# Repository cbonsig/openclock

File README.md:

openclock
=========

A clock designed to resolve the flaws of every annoying alarm clock that I've ever owned. Large display that can be easily read with uncorrected vision, adaptive brightness based on the time of day, intuitive touchscreen interface, clear feedback on the state of the alarm, intelligent alarm audio. Powered by Arduino. A work in progress. Journal of effort to date at http://clock.bonsignore.com

Open Clock Project by Craig Bonsignore is licensed under a Creative Commons Attribution-ShareAlike 3.0 United States License.Based on a work at http://clock.bonsignore.com.

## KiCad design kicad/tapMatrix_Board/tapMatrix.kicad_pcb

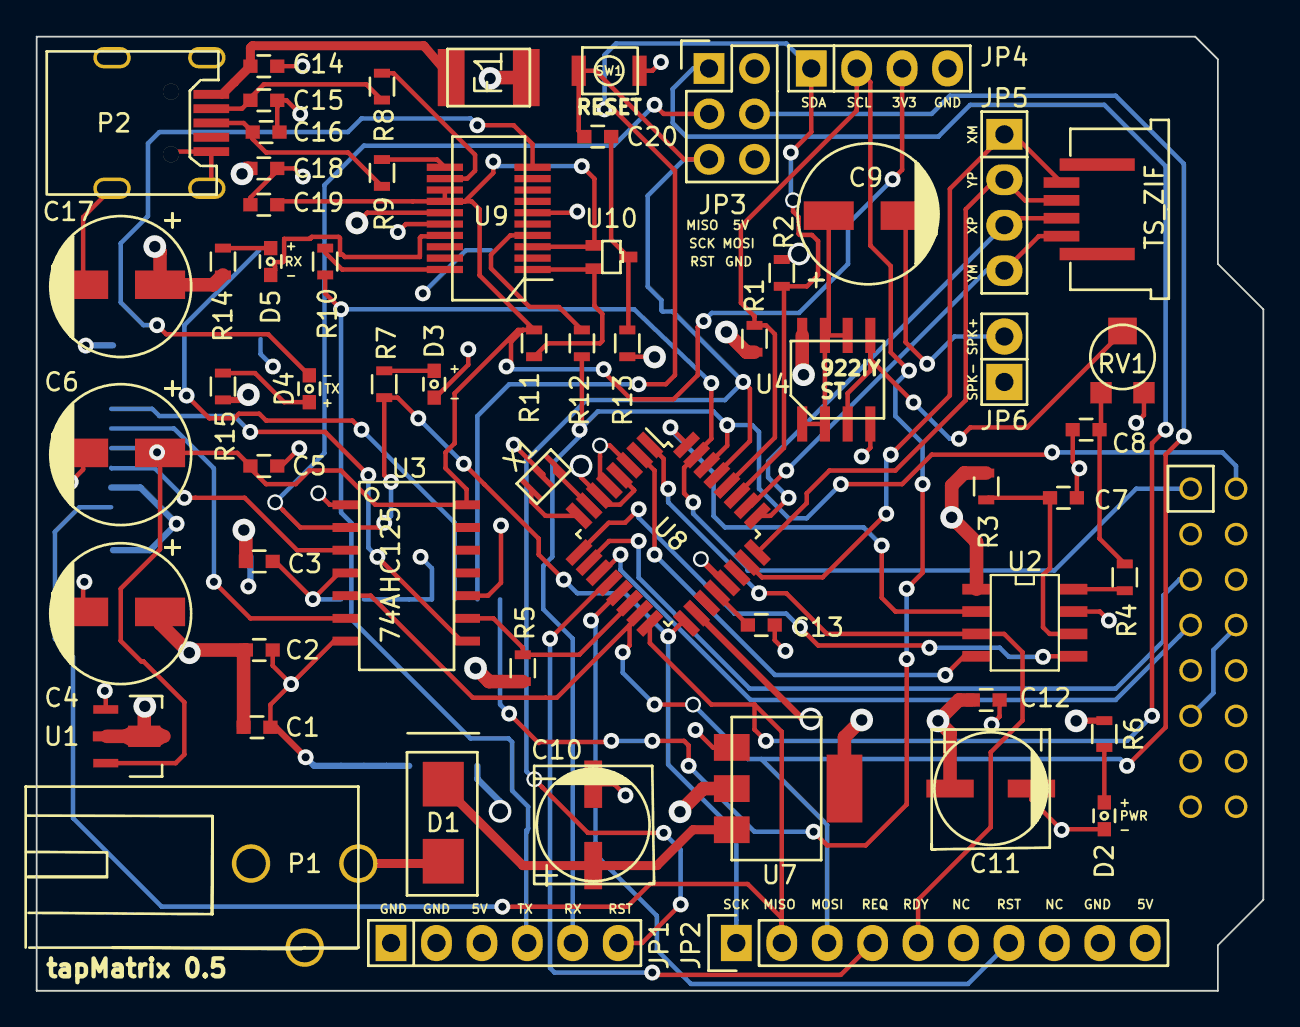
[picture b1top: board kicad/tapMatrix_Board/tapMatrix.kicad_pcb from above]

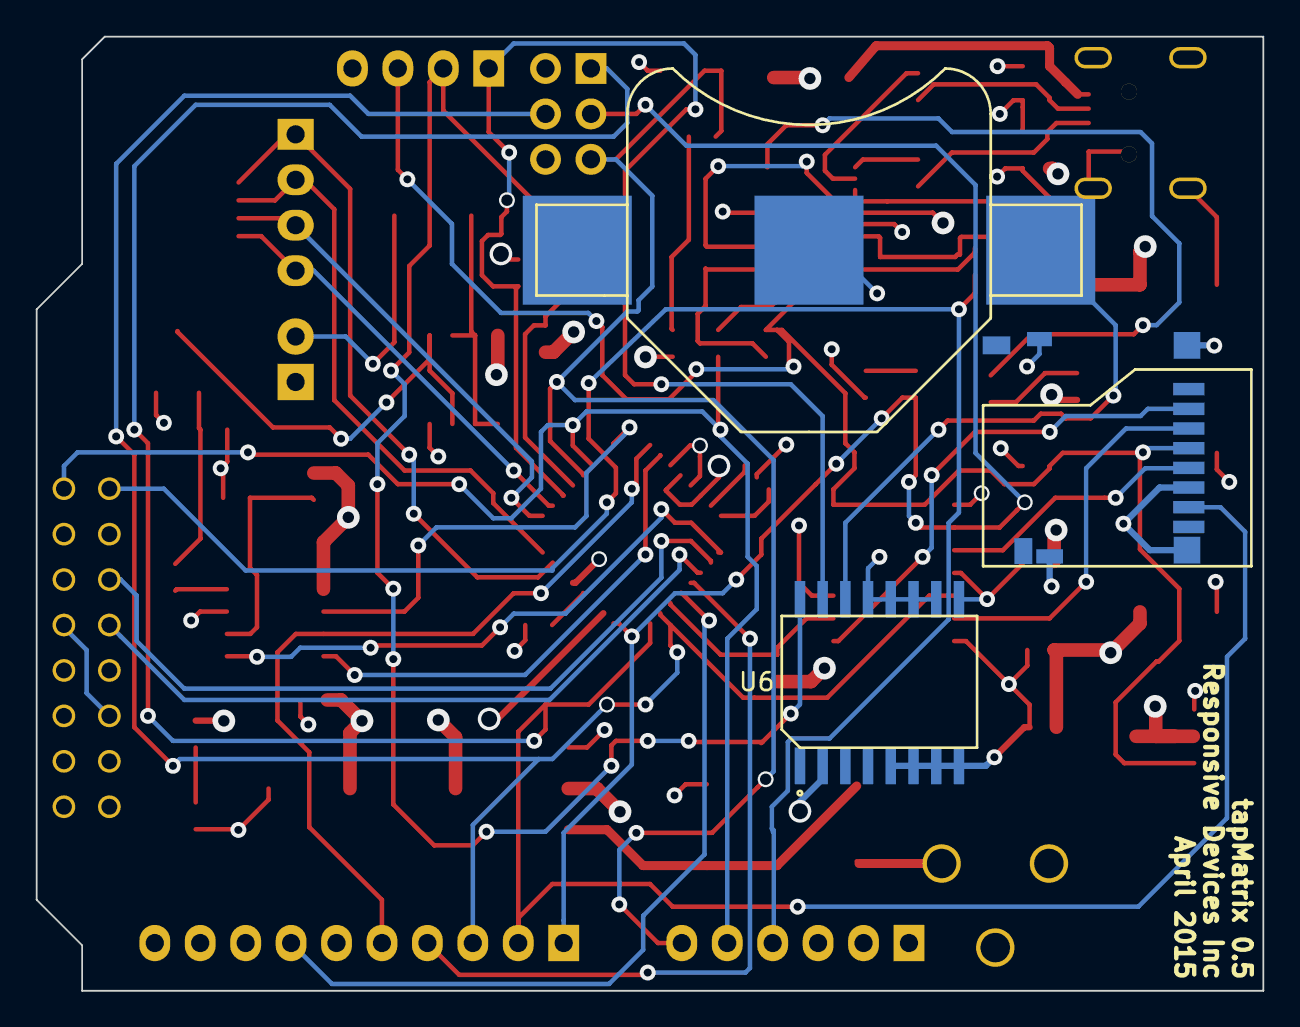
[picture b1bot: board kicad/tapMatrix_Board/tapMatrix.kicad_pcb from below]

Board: 4 copper layers, 68.6 x 53.3 mm, 65 parts (3 on the bottom side), 54 nets.

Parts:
BT1: BATTERY; CR2032
C1, C2, C3, C5, C7, C12, C13, C14, C18, C19, C20: 0.1uF; C_0603
C4, C6, C9: 100uF/6V; EEE-0JA101WR
C8: 0.01uF; C_0603
C10, C11: 47uF; CAP_MVA_F55
C15, C16: 47pF; C_0603
C17: 4.7uF; EEE-0JA101WR
D1: DIODE; DS16004
D2, D3: LED; D_0603
D4: TXLED; D_0603
D5: RXLED; D_0603
F1: 500mA; Fuse_MF_MSMF
JP1: FTDI; Pin_Header_Straight_1x06
JP2: nRF8001; Pin_Header_Straight_1x10
JP3: ICSP; Pin_Header_Straight_2x03
JP4: 4_PIN_2; Pin_Header_Straight_1x04
JP5: 4_PIN_1; Pin_Header_Straight_1x04
JP6: SPKR; Pin_Header_Straight_1x02
P1: +9V Power; PJ-102AH
P2: USB-MINI-B; USBMiniB_UX60_MB_5S8
P5: TS_ZIF; SFW4R­5STE1LF
P6: LED_MATRIX_HDR; 5103310­-3
R1, R2: R; R_0603
R3: 100K; R_0603
R4: 1.5K; R_0603
R5, R11, R13: 10K; R_0603
R6, R7: 510; R_0603
R8, R9: 27; R_0603
R10, R12, R14, R15: 1K; R_0603
RESET: SW_PUSH; SW_3BU_1000P
RV1: POT; TC33X
U1: MCP1703; SOT89-3_Housing
U2: MCP4921-E/SN; SOIC-8_N
U3: 74AHC125; SO-14
U4: TS922; TS922_SO8
U5: SD_CARD; 114-00841-68
U6: DS3231
U7: NCP1117ST50T3G; SOT223_318H
U8: ATMEGA328P-A; TQFP-32_7x7mm_Pitch0.8mm
U9: FT231XS; SSOP20_FTDI231X
U10: 2N7002PW; SOT-323
X1: CRYSTAL_SMD; XTAL_CSTCE_V

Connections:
+5V: C1.1, C2.1, C3.1, C4.1, C11.1, C12.1, C17.1, C18.1, F1.2, JP1.3, JP2.10, JP3.2, P6.12, P6.14, P6.16, R1.1, R2.1, R3.1, R5.1, R6.1, R13.1, R14.2, R15.2, U1.2, U2.1, U4.8, U6.2, U7.2, U8.4, U8.6, U8.18, U9.15
/CS: U3.8, U5.2
/D8: JP2.4, U8.12
/D9: JP2.7, U8.13
/DAC_CS: U2.2, U8.32
/DAC_DI: U2.4, U8.2
/DAC_LAT: U2.5, U8.9
/DAC_SCK: JP2.5, U2.3, U8.1
/DATA_IN: U3.6, U5.3
/I2C_SCL: JP4.2, R1.2, U6.16, U8.28
/I2C_SDA: JP4.1, R2.2, U6.15, U8.27
/MATRIX_CLK: JP1.5, P6.2, R12.2, U8.30
/MATRIX_CS: JP1.4, P6.1, R10.2, U8.31
/MATRIX_DATA: P6.7, U8.11
/MATRIX_WR: P6.5, U8.10
/MISO: JP2.2, JP3.1, U5.7, U8.16
/MOSI: JP2.3, JP3.4, U3.5, U8.15
/RESET: C20.1, JP1.6, JP3.5, RESET.2, U8.29
/SCK: JP2.1, JP3.3, R7.2, U3.2, U8.17
/SCLK: U3.3, U5.5
/SD_CS: R5.2, U3.9, U8.14
/XM: JP5.1, P5.1, U8.23
/XP: JP5.3, P5.3, U8.25
/YM: JP5.4, P5.4, U8.26
/YP: JP5.2, P5.2, U8.24
GND: BT1.2, C1.2, C2.2, C3.2, C4.2, C5.2, C6.2, C7.1, C8.2, C10.2, C11.2, C12.2, C13.2, C14.2, C15.2, C16.2, C17.2, C18.2, C19.2, D2.2, D3.2, JP1.1, JP1.2, JP2.9, JP3.6, JP4.4, JP6.1, P1.2, P1.3, P2.5, P2.6, P2.7, P2.8, P2.9, P6.8, P6.11, P6.13, P6.15, RESET.1, RV1.3, U1.1, U2.7, U3.1, U3.4, U3.7, U3.10, U4.4, U5.6, U5.G1, U5.G2, U5.G3, U5.G4, U6.5, U6.6, U6.7, U6.8, U6.9, U6.10, U6.11, U6.12, U6.13, U7.1, U8.3, U8.5, U8.21, U9.6, U9.16, X1.2
unnamed: BT1.1, U6.14
unnamed: C7.2, R3.2, U2.6
unnamed: C8.1, R4.1, RV1.1
unnamed: C9.1, U4.1, U4.2, U4.6, U4.7
unnamed: C9.2, JP6.2
unnamed: C10.1, D1.2, U7.3
unnamed: C13.1, U8.20
unnamed: C14.1, F1.1, P2.1
unnamed: C15.1, P2.2, R8.1
unnamed: C16.1, P2.3, R9.1
unnamed: C20.2, R13.2, U10.3
unnamed: D1.1, P1.1
unnamed: D2.1, R6.2
unnamed: D3.1, R7.1
unnamed: D4.1, R15.1
unnamed: D4.2, U9.10
unnamed: D5.1, R14.1
unnamed: D5.2, U9.17
unnamed: R4.2, U2.8
unnamed: R8.2, U9.12
unnamed: R9.2, U9.11
unnamed: R10.1, U9.20
unnamed: R11.2, U9.1, U10.2
unnamed: R12.1, U9.4
unnamed: RV1.2, U4.3, U4.5
unnamed: U8.7, X1.1
unnamed: U8.8, X1.3
VCC: C5.1, C6.1, C19.1, JP4.3, R11.1, U1.3, U3.14, U5.4, U9.3, U9.13, U9.14, U10.1

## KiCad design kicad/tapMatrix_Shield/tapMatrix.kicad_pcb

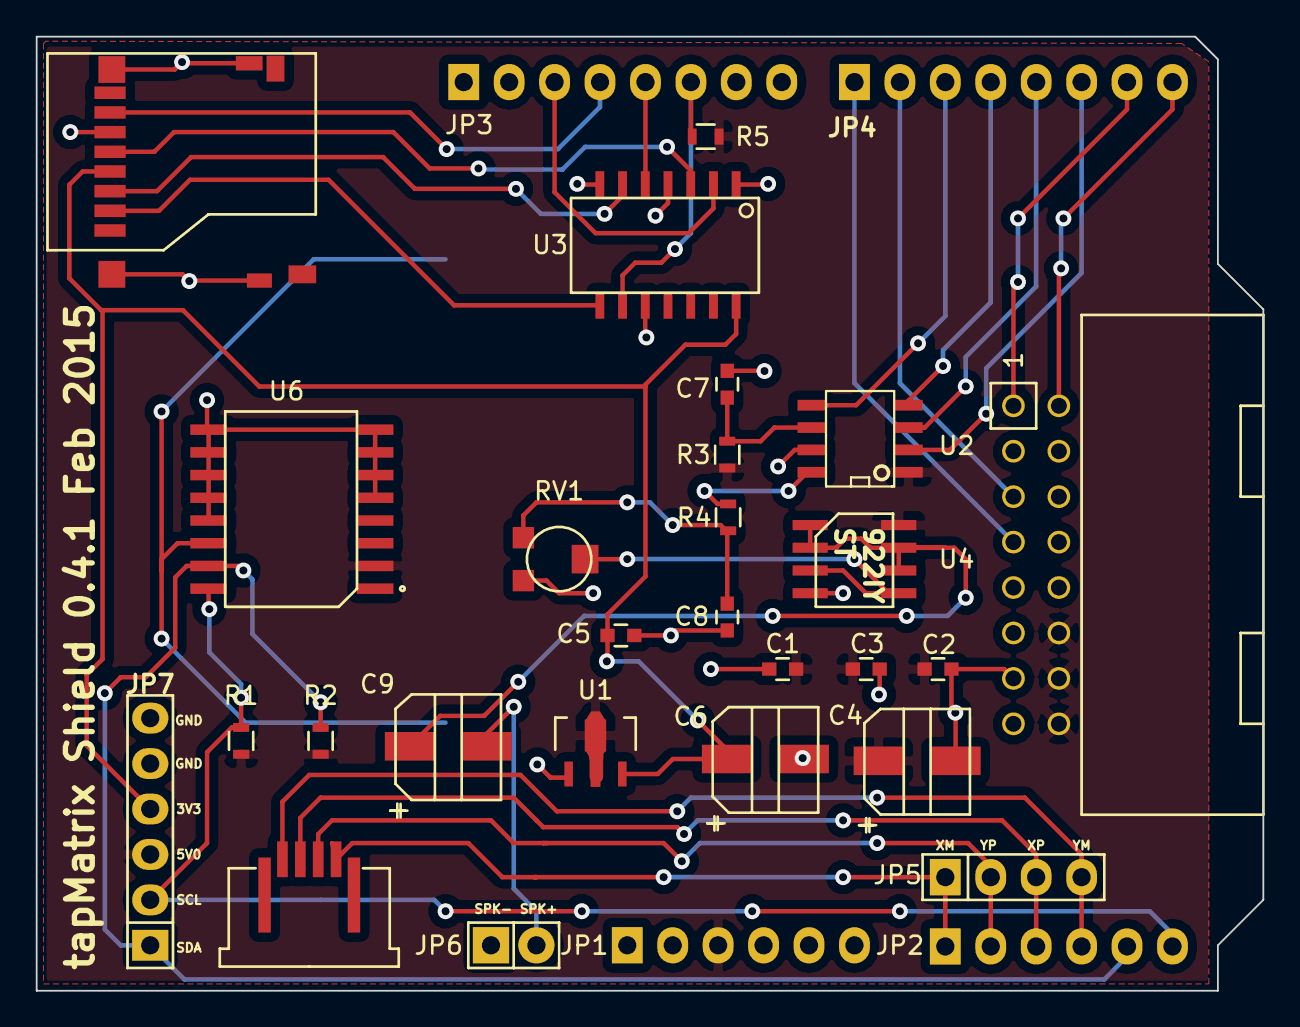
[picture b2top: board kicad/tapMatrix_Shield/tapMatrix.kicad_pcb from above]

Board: 2 copper layers, 68.6 x 53.3 mm, 31 parts (1 on the bottom side), 31 nets.

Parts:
BT1: CR2032
C1, C2, C3, C5, C7: 0.1uF; C_0603
C4, C6, C9: 100uF/6V; EEE-0JA101WR
C8: 0.01uF; C_0603
JP1: 6_PIN_1; Pin_Header_Straight_1x06
JP2: 6_PIN_2; Pin_Header_Straight_1x06
JP3: 8_PIN_1; Pin_Header_Straight_1x08
JP4: 8_PIN_2; Pin_Header_Straight_1x08
JP5: 4_PIN_1; Pin_Header_Straight_1x04
JP6: SPKR; Pin_Header_Straight_1x02
JP7: 6_PIN_3; Pin_Header_Straight_1x06
P5: TS_ZIF; SFW4R­5STE1LF
P6: LED_MATRIX_HDR; 5103310­-3
R1, R2: R; R_0603
R3: 100K; R_0603
R4: 1.5K; R_0603
R5: 10K; R_0603
RV1: POT; TC33X
U1: MCP1703; SOT89-3_Housing
U2: MCP4921-E/SN; SOIC-8_N
U3: 74LS125; SO-14
U4: TS922; TS922_SO8
U5: SD_CARD; 114-00841-68
U6: DS3231

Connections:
+3.3V: C5.1, C6.1, JP7.4, U1.3, U3.14, U5.4
+5V: C1.1, C2.1, C3.1, C4.1, JP1.3, JP7.3, P6.12, P6.14, P6.16, R1.1, R2.1, R3.1, R5.1, U1.2, U2.1, U4.8, U6.2
/CS: U3.8, U5.2
/DAC_CS: JP4.6, U2.2
/DAC_DI: JP4.4, U2.4
/DAC_LAT: JP4.3, U2.5
/DAC_SCK: JP4.5, U2.3
/DATA_IN: U3.6, U5.3
/I2C_SCL: JP2.6, JP7.2, R1.2, U6.16
/I2C_SDA: JP2.5, JP7.1, R2.2, U6.15
/MATRIX_CLK: JP4.8, P6.2
/MATRIX_CS: JP4.7, P6.1
/MATRIX_DATA: JP4.1, P6.7
/MATRIX_WR: JP4.2, P6.5
/MISO: JP3.4, U5.7
/MOSI: JP3.5, U3.5
/SCK: JP3.3, U3.2
/SCLK: U3.3, U5.5
/SD_CS: JP3.6, R5.2, U3.9
/XM: JP2.1, JP5.1, P5.1
/XP: JP2.3, JP5.3, P5.3
/YM: JP2.4, JP5.4, P5.4
/YP: JP2.2, JP5.2, P5.2
GND: BT1.2, C1.2, C2.2, C3.2, C4.2, C5.2, C6.2, C7.1, C8.2, JP1.4, JP1.5, JP3.2, JP6.1, JP7.5, JP7.6, P6.8, P6.11, P6.13, P6.15, RV1.3, U1.1, U2.7, U3.1, U3.4, U3.7, U3.10, U4.4, U5.6, U5.G1, U5.G2, U5.G3, U5.G4, U6.5, U6.6, U6.7, U6.8, U6.9, U6.10, U6.11, U6.12, U6.13
unnamed: BT1.1, U6.14
unnamed: C7.2, R3.2, U2.6
unnamed: C8.1, R4.1, RV1.1
unnamed: C9.1, U4.1, U4.2, U4.6, U4.7
unnamed: C9.2, JP6.2
unnamed: R4.2, U2.8
unnamed: RV1.2, U4.3, U4.5

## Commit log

2012-08-22 Initial commit for sketches and related libraries
2012-08-22 Add Solidworks parts and assembly
2012-08-26 Update README.md
    Add description of project.
2012-08-26 Update README.md
    Add reference to CC Attribution-ShareAlike 3.0 license
2012-11-17 rename to openclock.ino
    renamed the file and directory for the main sketch. this and future
    revisions will be managed by githib.
2012-11-25 rewrite to make code more organized
    move contributed libraries to sketch folder, per Arduino 1.0.2
    guidance. major refactoring . created currentTime subroutine . all
    characters now defined by global variables . all characters drawn to
    screen in one place @ end of main loop(). preparation for adding a
    functional UI to set time and alarm . added draft flow diagram for UI
2012-12-03 refactoring and touch development
    more reorganization of the code, and development of the touch routines.
    currently message area displays x,y,z when touch pressure exceeds
    threshold. to do: assign a timer to touch events, map touch events to
    menu selections and +/- digits.
2012-12-03 Update openclock/openclock.ino
    Added a link to an explanation about why using a pin higher than 8 does not work.
2012-12-03 Fixed hour bug
2012-12-04 Virtual button development
    Touch activated virtual buttons [hr+], [hr-], [min+], [min-], [ampm],
    [msg] can be detected, and will be used later for menu, alarm, and
    set-time functions. For now, the button state is displayed in the
    message area.
2012-12-04 ix bug: midnight renders as 0:00
2012-12-04 Revert "ix bug: midnight renders as 0:00"
    This reverts commit d720b7c31345ddba16c0d397b14fbf2bdf63aabc.
2012-12-04 Revert "Revert "ix bug: midnight renders as 0:00""
    This reverts commit 11733e3db17b308eef8b654cf0011cb639cfc867.
2012-12-10 Beginning code for alarm mode
    Added barely functional code for entering alarm set mode, and setting
    the alarm time.
2012-12-17 Replace <Chronodot.h> with Arduino Time Library
    Swapped out Chronodot library for the Arduino Time Library to be more
    standardized. Auto-formatted to fix indent levels.
2013-02-05 reworked touch and menu functions
    improved functionality of alarm setting mode. Not quite prefected.
    Menu timer isn't resetting for some reason.
2013-02-10 temporary sketch feb09
    (throretically) improved timers by moving initiation to setup as
    intended... now, first entry into menu mode works perfectly… but,
    second entry into menu mode never returns to clock mode. can't upload
    this to clock, so i'm stashing it here for now, as sketch_feb09a
2013-02-27 UI design refinements
    Mock-ups of menu modes, and draft additions to flow chart
2013-03-03 major rewrite for menu/tap timers
2013-03-04 Debug + Rearrange menus
    Halfway implemented new menu scheme. TBD: revise display rendering for
    display states.
2013-03-05 Rough code for menu scheme completed
    Rough code for menu scheme completed. TBD: code RTC commits for alarm
    and time; fix handling of time set.
2013-03-06 debug . display logic refinement
2013-03-08 color change for alarm display; display formatting
2013-03-08 fix alarm color display, fix incrementation for am/pm
2013-03-08 add RTC commit for time
    added RTC commit for time (with a couple of days to go before DST
    begins!!)
2013-03-09 Fix date setting screens, add alarm on/off toggle
2013-03-09 minor edits. changed most int to byte
2013-03-10 Revert byte to int for tapZone and displayState to fix time set bug
2013-03-12 Fix set year display bug (20-1)
    Revert newYear from byte to int
2013-03-12 fix alarm color rendering on main screen
2013-03-12 Commenting improvements
2013-03-16 Reduce SRAM footprint by 32 bytes (not enough)
2013-03-16 Add Waveshield and cleanup
2013-03-16 Cleanup and waveshield
2013-03-17 Waveshield victory!
    Added Waveshield setup{} code, and confirmed audio functionality.
    CLK_TOWR.WAV is played when EXIT is selected from menu.
2013-03-17 prep for alarm. change alarmState from boolean to byte
    prep for alarm. change alarmState from boolean to byte. add #define
    lines for alarm states including active and snooze
2013-03-17 checkAlarm() added, basic alarm function working!
2013-03-17 reference interrupt thread
2013-03-31 Correct year display
    Fix display of year for case where year = 2000 (default year for new
    chronodot)
2013-03-31 Add clock sounds .WAV files
2013-04-10 Created folders for 3D enclosure and 2D enclosure designs
    Moved OpenClockSolidworks to enclosure_design/3D_rev1 and created
    enclosure_design/2D_rev1 with Inkscape, LibreCAD, and SolidWorks files
2013-04-20 Update Rev1 2D enclosure
    Revised SVG for 2D Rev 1 ("Box") enclosure based on small modifications
    required on first laser cut prototype.
2013-04-22 Enclosure Rev1A updates
2013-05-03 2d rev 2 curved enclosure, solidworks in progress
2013-05-04 Curved 2D Enclosure - Solidworks
    complete solidworks geometry for rev2 enclosure
2013-05-04 nothing to see here
2013-05-05 Updates to Solidworks enclosure design
2013-05-05 Enclosure Design
    Curved enclosure design in Solidworks + Inkscape
2013-05-05 Inkscape 2D design for enclosure
2013-10-08 Overdue update to SVG design. The _1315 version is the one that was actually cut.
2014-03-02 update gitignore
2014-03-02 admin
2014-08-17 Initial commit for KiCad project and empty schematic
2014-08-18 Added Arduino headers to schematic
2014-08-18 Added ZIF socket, created component library, fixed Arduino headers
2014-08-19 add led matrix header, microsd component, update libraries
2014-08-20 improved headers, replaced global labels with local labels
2014-08-21 confirm and revise quad-buffer and microsd schematic details
2014-08-22 add 3.3V power supply, DAC, AMP, and Speaker Out
2014-08-23 add real time clock to schematic
2014-08-24 schematic edits to resolve error checking messages
2014-08-25 added footprints for battery and ribbon sockets
2014-08-25 created power and signal netclasses, updated design rules for oshpark
2014-08-26 add microsd module
2014-08-27 begin routing pcb
2014-08-27 continue routing
2014-08-29 complete first attempt at routing
2014-08-29 removed volume pot; created gerber files
2014-08-29 Add .gitignore
2014-08-29 reference local ht1632c library
2014-09-02 replaced 100uF caps with avail footprint; moved vias; revised to 0.2;
2014-09-04 added optional 4-pin header as alt for touchscreen zif
2014-09-04 trying to get rid of .DS_store pollution
2014-09-04 more DS_store erradiction
2014-09-04 replace voltage regulator with corrected component
2014-09-04 update gerbers for revision to voltage regulator component
2014-09-04 add top and bottom solder paste layers to gerbers
2014-09-23 create v0.3_ fix problems with U1, U3, U4 components U1 used the wrong footprint. changed from SOT-23 to SOT-89-3 U3 used the narrow version of SOIC-14 (incorrectly named in library as SOIC-14_W). ch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
2014-10-24 Add data sheets for new 0.3 components
2014-10-27 Revised r0.3 components, tore up pcb
2014-10-28 move capacitor footprints to tapmatrix library
2014-10-28 move resistor footprints to tapmatrix library
2014-10-28 catch up with commits for moving R and C to tapmatrix library
2014-10-28 move pin header footprints to tapmatrix library
2014-10-28 move SOT-89-3 footprint to tapmatrix library
2014-10-28 moved SOIC footprints to tapmatrix library
2014-10-31 confirmed and revised IC footprints
2014-11-01 route v3 pcb, first draft
2014-11-01 resolved DRC errors in v0.3 layout
2014-11-01 clean up labels
2014-11-02 corrected duplicated .zip.zip extension
2014-11-02 revised layout to improve GND and +5V plane connectivity
2014-11-02 added paste files to gerbers for stencil. updated dwg revision date.
2014-11-03 revised C3 to link to tapMatrix library, other minor edits
    re-routed C3
    repositioned reference labels for caps
    changed U1 line width to be consistent with other components
2014-11-03 Revise data sheet filenames to be more descriptive
2014-11-03 add datasheet for micro-SD connector
2014-11-03 PNG of uSD
2014-11-03 corrected uSD connector footprint
2014-11-03 add overlay of uSD datasheet and footprint
2014-11-24 corrected error with U1 pins (2 and 3 were reversed)
2014-11-24 corrected JP4, where MATRIX_WR and MATRIX_DATA were reveresed
2014-11-24 Add data sheet for DAC
2014-12-15 Revised Arduino code for shield v0.3
    Reordered touchscreen wires A0-A3
2014-12-16 Add comment regarding RTC fix
2014-12-24 Add data sheets for DS3231 trimpot and TS922 opamp
2014-12-24 Updated schematic annotations
2014-12-24 Schematic: replaced RTC and added pot replaced DS1207 with DS3231 real time clock added potentiometer to amplifier circuit
2014-12-25 add footprints and headers, tear up layout
2014-12-25 revise schematic
2015-01-05 save project
2015-02-04 Correct reversed pins 2+3 on LDO
    Input and output pins were reversed on the MCP1703 voltage regulator.
    Corrected schematic, footprint, and layout.
2015-02-04 draft 4-layer version of board
2015-02-14 0.4.1 revision - new level shifter component, etc
    Replace quad buffer / level shifter with 74AHC125N components tolerant
    of VCC=3.3V. Correct mixed pins on LDO. Add labels for breakout pins,
    and refine silkscreen text.
2015-02-19 Start rev 0.5 board
2015-02-20 complete first draft of 0.5 board
    add headers for FTDI, I2C, other extra pins.
2015-02-21 Add ICSP header and power LED
2015-03-17 Add FTDI USB-UART
    Added schematics for FTDI, based on Sparkfun Redboard and FTDI
    reference schematics. Created symbols for FT231XS and 2N7002PW.
2015-03-17 Revised schematic for FTDI
2015-03-31 Add SPI header for nRF8001
2015-03-31 Datasheets + Footprints for 5V supply circuit
2015-04-01 Datasheets + Footprints for AT328p, XTAL, Fuse, USB, FTDI
2015-04-02 cosmetic updates to schematic
2015-04-02 Complete footprint association and netlist definition
2015-04-02 Modify JP2 from 6pin to 10pin header
2015-04-02 Correct nettles and camp association for JP2
2015-04-03 Rough placement of footprints
2015-04-04 add C20, begin routing
2015-04-06 continue routing top layer
2015-04-07 Complete first pass routing
2015-04-09 Complete routing of 4-layer board
2015-04-10 Complete routing and formatting, create Gerbers

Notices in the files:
kicad/tapMatrix_Shield/tapMatrix.kicad_pcb:
(c) 2015 Responsive Devices Inc
